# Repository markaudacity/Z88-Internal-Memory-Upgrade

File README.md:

# Z88 Internal Memory Upgrade Board

**This is a very alpha-stage design for a single-board internal RAM/Flash ROM upgrade for the Cambridge Z88 computer.**

&nbsp;

## Background
The Z88 can address up to 4 MB of RAM and ROM in three physical expansion slots and the internal RAM and ROM. Since the internal RAM and ROM are addressed as logical slot 0, they can use the full address space, which is not used by the base 32 kB RAM and 128 kB ROM. Normally to upgrade internal memory like this, one would just desolder the original RAM and ROM, replace them with sockets, and install new flash and bigger RAM, but in the Z88, there is both: 
1) very little room between the board and the keyboard frame, and
2) the existing chip footprint does not have the A17 and A18 address lines required to increase the RAM and ROM to 512kB, from 32kB and 128kB, respectively.

There is an existing mod to upgrade the internal memory that has been floating around since some time in the early 90s, which involves lifting pins on the replacement 512 kB flash and SRAM chips and soldering three or four fly wires to various locations on the board. Very much not a straightforward job, and the best writeup for it available on the internet has at least two of the address lines mislabeled, so the top two address bits are flipped. This doesn't really matter for RAM, since everything is going to be written with those same address lines swapped, but it sure does for the ROM. I chased this around for several hours over a few weeks before I realized the writeup had it wrong. 

Since the A17 and A18 address lines and slot-select lines are all available on vias, I had the idea to create a board that has pins at the corresponding locations that can simply be soldered into place like any other through-hole device. Originally, this was going to have pin headers duplicating the legs of both DIP devices, which was a hassle. About halfway through trying to design a board with all those traces routed around 56 through-hole pins, I realized that since both original memory devices were on the same bus and both have very similar pinouts, many of the necessary signals were duplicated such that only the two outer rows of pins are needed from each original footprint. This saves many pins and holes, both of which cost money, as well as making the traces MUCH easier to route without having to dodge around all the extra pins.
## Current Status
As of March 2026, I have still not had boards made or soldered up any prototypes, so if you build one of these, it is the most YMMV, do-so-at-your-own-risk, safety-third, hold-my-beer project.
## What's Been Done
- Z88 motherboard traces followed and holes measured, to make sure we're pulling the right signals and putting the pins in the right places
- the uhhhh basic design lol
- models made for the Mill-Max DIP-sized pin headers, which are smaller in diameter and shorter overall than Dupont header pins, which will not fit in holes drilled for DIP pins
- bypass caps added, to prove I'm not a scrub-ass n00b *[I am a scrub-ass n00b]*

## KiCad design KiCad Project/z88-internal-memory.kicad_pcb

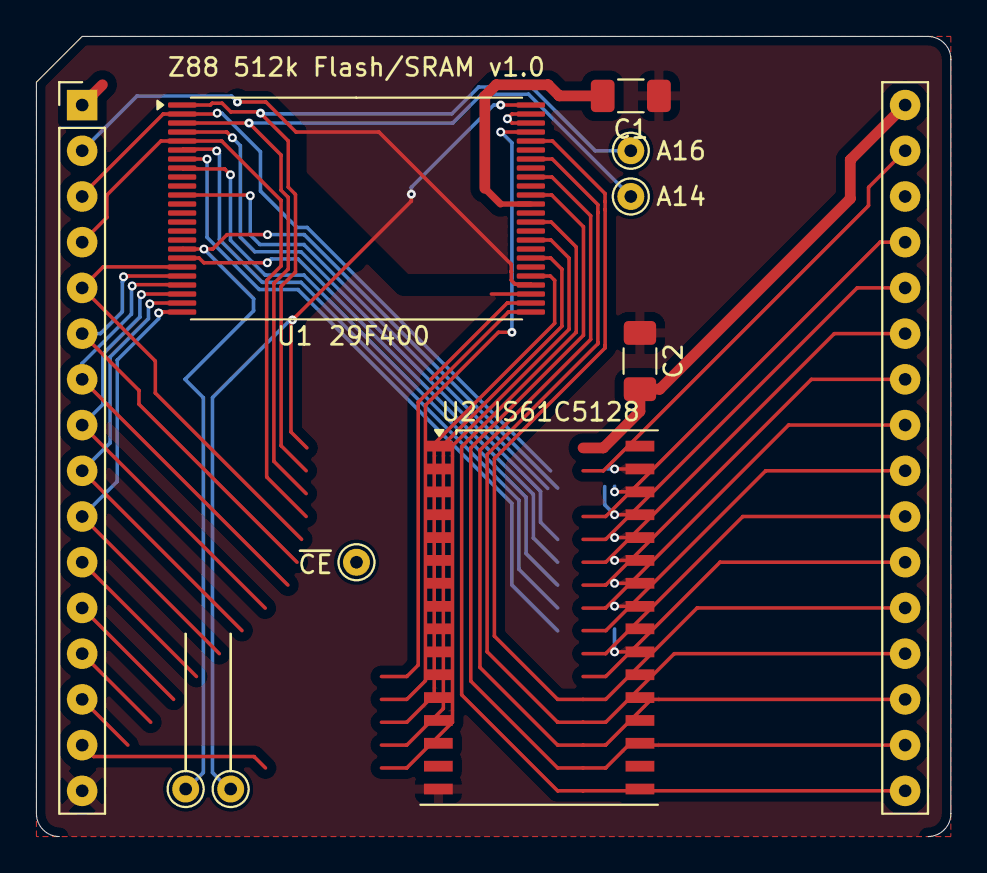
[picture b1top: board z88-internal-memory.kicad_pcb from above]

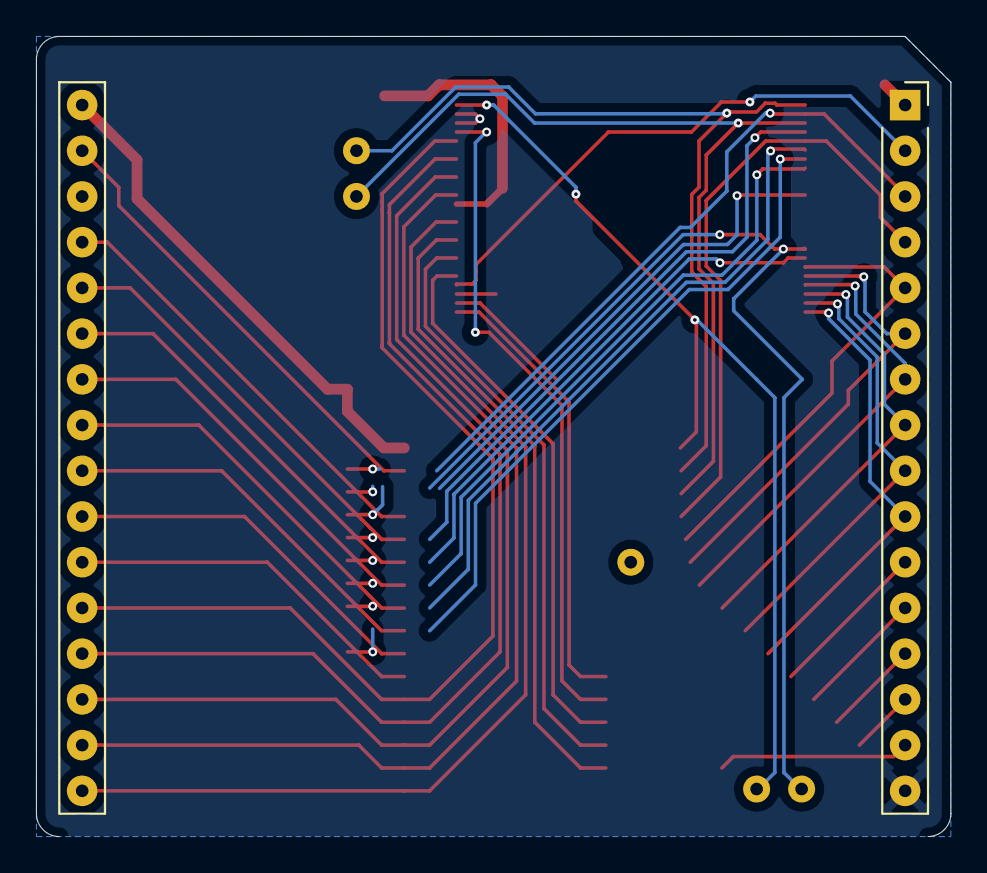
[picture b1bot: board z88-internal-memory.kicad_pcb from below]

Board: 2 copper layers, 50.8 x 44.4 mm, 11 parts (2 on the bottom side), 34 nets.

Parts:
C1, C2: 100 nF; C_1206_3216Metric_Pad1.33x1.80mm_HandSolder
P1: SIPHeader_1x16_Vertical_P1
P3: SIPHeader_1x16_Vertical
TP1: ~{CE}; TestPoint
TP2: A14; TestPoint
TP3: A16; TestPoint
TP4, TP5: TestPoint
U1: 29F400; TSOP-I-48_18.4x12mm_P0.5mm
U2: IS61C5128; TSOP-II-32_21.0x10.2mm_P1.27mm

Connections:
/A0: P1.12 (A0), U1.45 (DQ15/A-1), U2.12 (A0)
/A1: P1.11 (A1), U1.25 (A0), U2.11 (A1)
/A2: P1.10 (A2), U1.24 (A1), U2.10 (A2)
/A3: P1.9 (A3), U1.23 (A2), U2.9 (A3)
/A4: P1.8 (A4), U1.22 (A3), U2.8 (A4)
/A5: P1.7 (A5), U1.21 (A4), U2.7 (A5)
/A6: P1.6 (A6), U1.20 (A5), U2.6 (A6)
/A7: P1.5 (A7), U1.19 (A6), U2.5 (A7)
/A8: P3.27 (A8), U1.18 (A7), U2.27 (A8)
/A9: P3.26 (A9), U1.8 (A8), U2.26 (A9)
/A10: P3.23 (A10), U1.7 (A9), U2.23 (A10)
/A11: P3.25 (A11), U1.6 (A10), U2.25 (A11)
/A12: P1.4 (A12), U1.5 (A11), U2.4 (A12)
/A13: P3.28 (A13), U1.4 (A12), U2.28 (A13)
/A14: TP2.1, U1.3 (A13), U2.3 (A14)
/A15: P1.3 (A15), P3.31 (A15), U1.2 (A14), U2.31 (A15)
/A16: TP3.1, U1.1 (A15), U2.2 (A16)
/A17: TP4.1, U1.48 (A16), U2.1 (A17)
/A18: TP5.1, U1.17 (A17), U2.30 (A18)
/D0: P1.13 (D0), U1.29 (DQ0), U2.13 (I/O0)
/D1: P1.14 (D1), U1.31 (DQ1), U2.14 (I/O1)
/D2: P1.15 (D2), U1.33 (DQ2), U2.15 (I/O2)
/D3: P3.17 (D3), U1.35 (DQ3), U2.17 (I/O3)
/D4: P3.18 (D4), U1.38 (DQ4), U2.18 (I/O4)
/D5: P3.19 (D5), U1.40 (DQ5), U2.19 (I/O5)
/D6: P3.20 (D6), U1.42 (DQ6), U2.20 (I/O6)
/D7: P3.21 (D7), U1.44 (DQ7), U2.21 (I/O7)
/~IPCE: TP1.1, U1.26 (~CE)
/~IRCE: P3.22 (~CS1), U2.22 (~CE)
/~OE: P3.24 (~OE), U2.24 (~OE)
/~ROE: P1.2 (~OE), U1.28 (~OE)
/~WE: P3.29 (~WE), U1.11 (~WE), U2.29 (~WE)
GND: C1.1, C2.1, P1.16 (VSS), U1.27 (VSS), U1.46 (VSS), U1.47 (~BYTE), U2.16 (GND)
VCC: C1.2, C2.2, P1.1 (VPP), P3.32 (Vcc), U1.37 (VCC), U2.32 (VDD)

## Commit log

2025-01-06 rearrange
2025-01-06 reorganize
2025-01-07 tweaks
2025-01-07 imaages
2025-01-07 updated silkscreen
2025-01-10 layout tweaks, added correct machined-pin headers
    3D model and new footprint for pin headers, with silkscreening for back of board mounting
2025-01-10 updated images
2025-01-10 deleted DS_Store files
2026-03-19 added bypass caps, pre-production tweaks
2026-03-19 Update README.md, add pictures
2026-03-19 rearranging directory for better clarity
2026-05-15 progressive update
